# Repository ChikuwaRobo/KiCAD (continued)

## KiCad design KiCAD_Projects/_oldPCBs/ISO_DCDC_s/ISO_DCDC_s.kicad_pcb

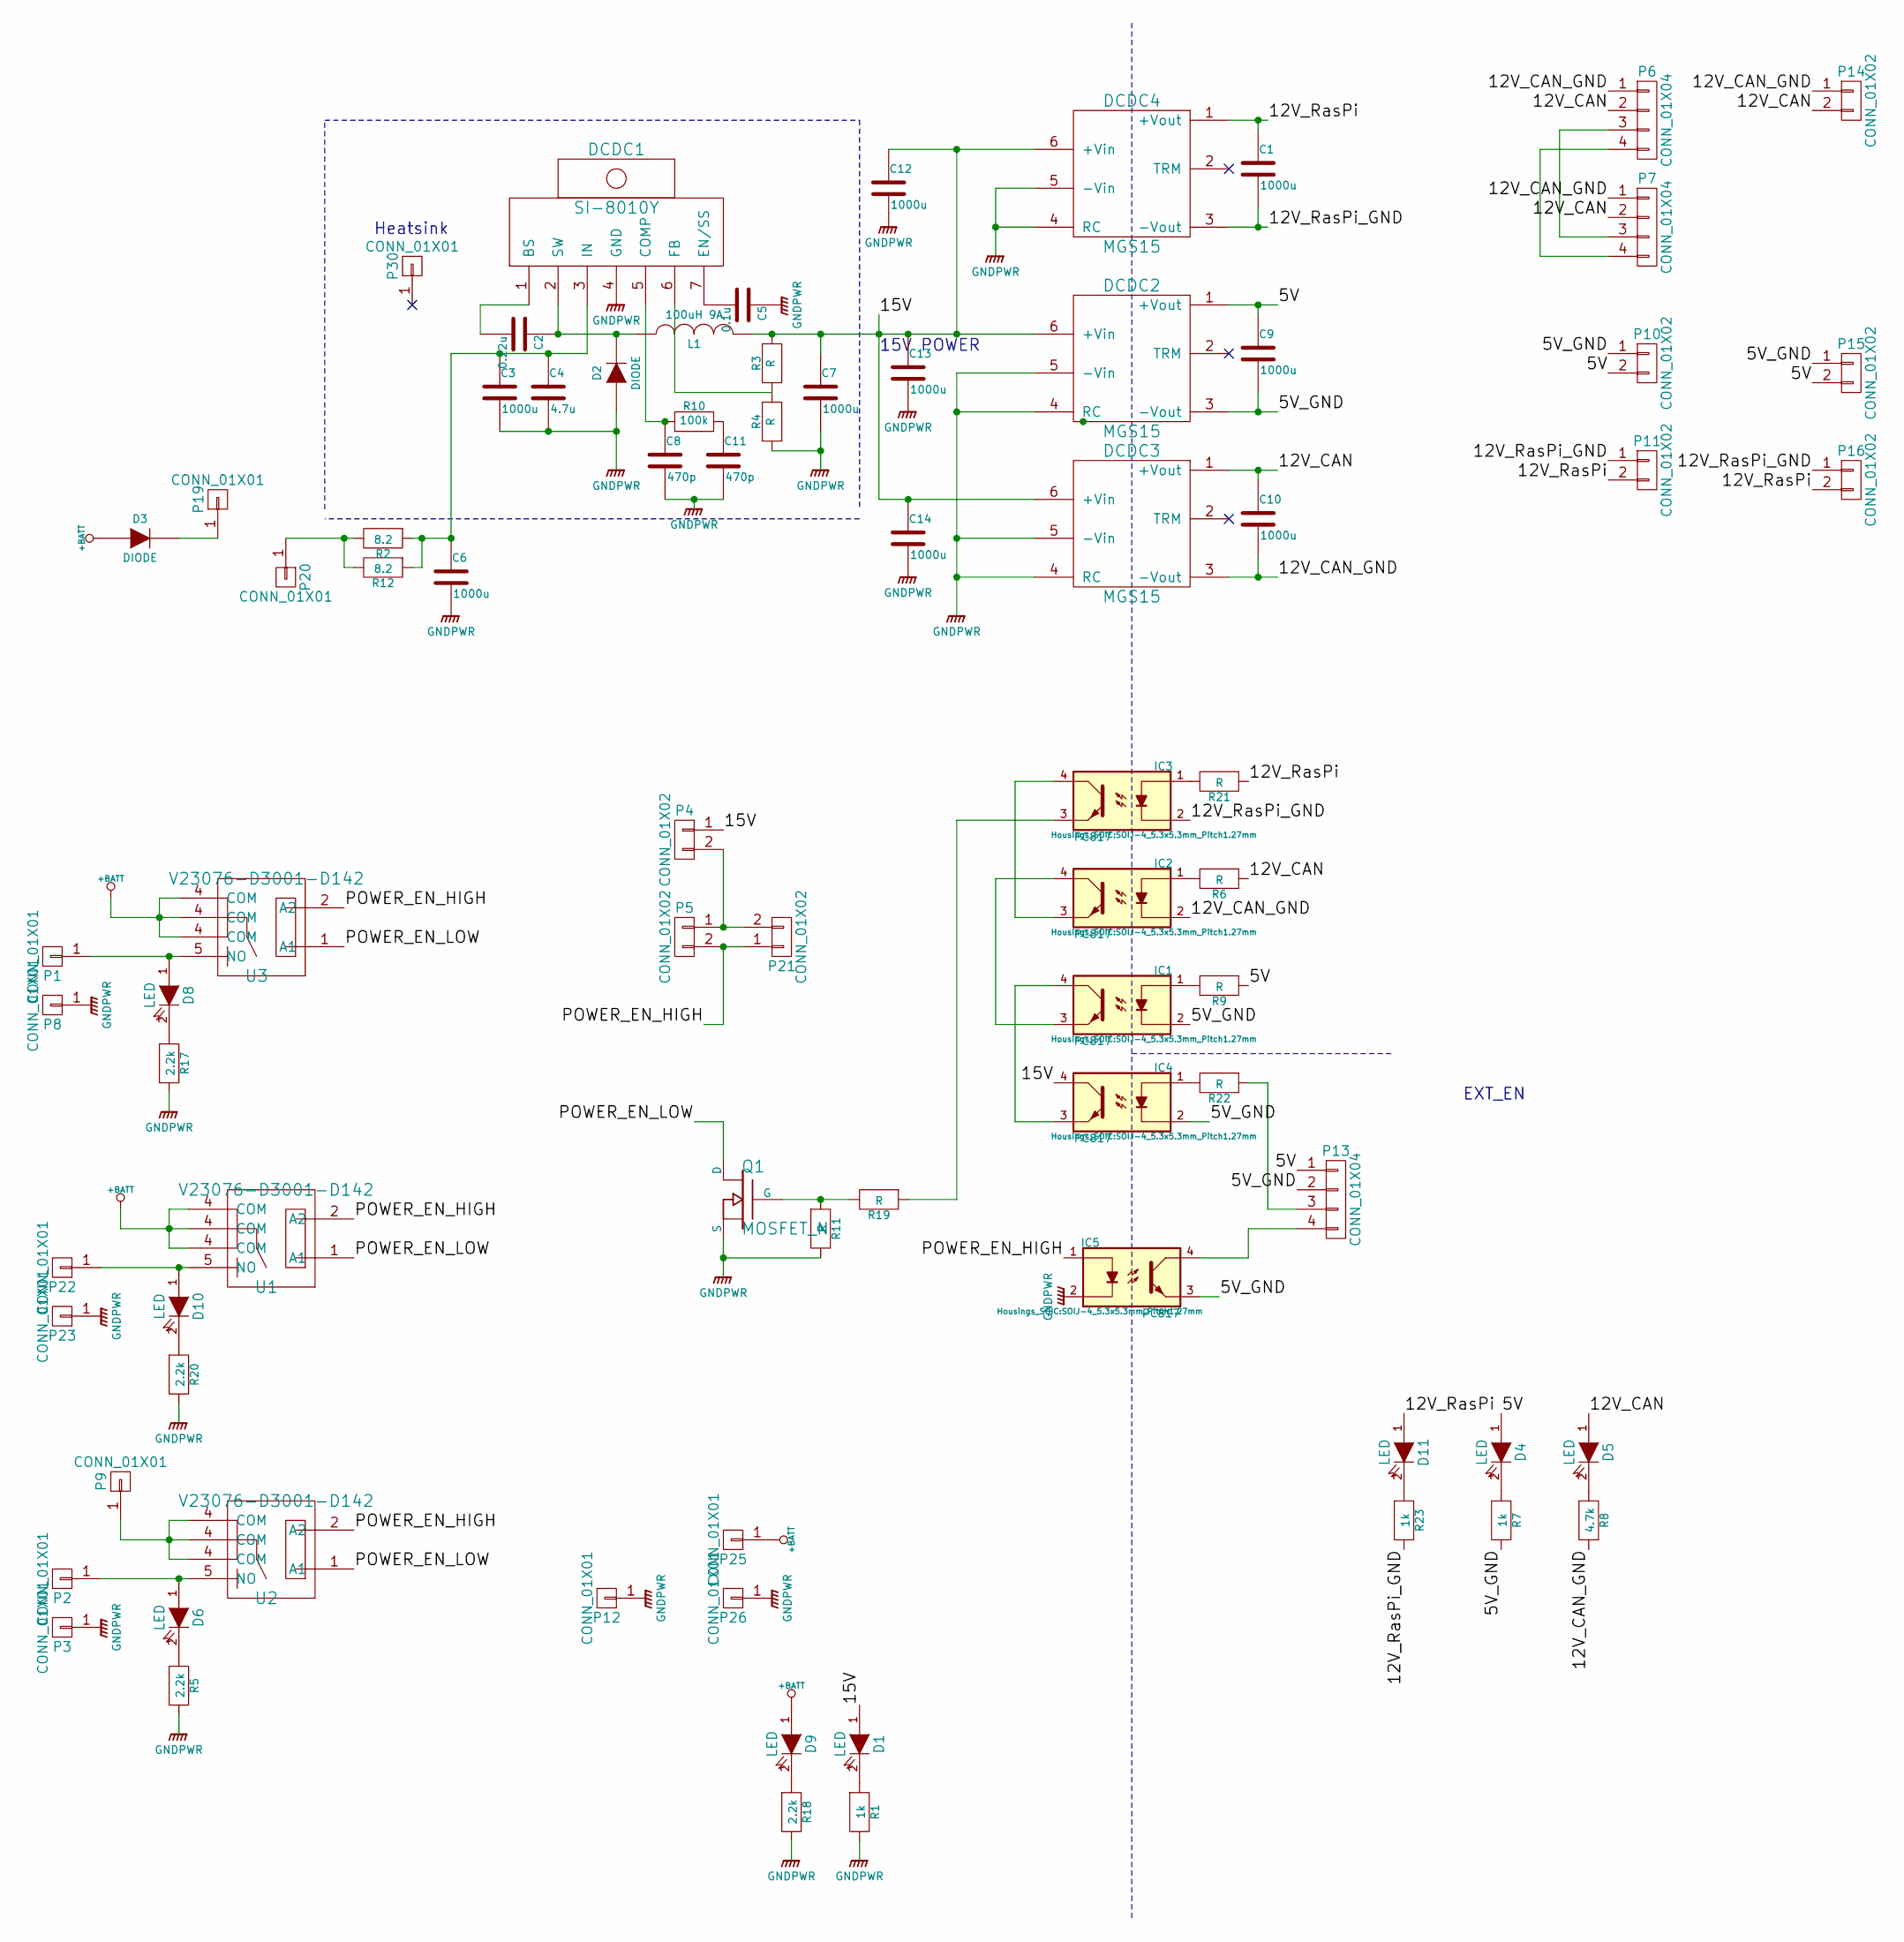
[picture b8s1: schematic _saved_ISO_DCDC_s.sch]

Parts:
C1, C9, C10: 1000u; C_Radial_D8_L11.5_P3.5
C2: 0.22u; C1608_WP
C3, C6, C7, C12, C13, C14: 1000u; C_Radial_D10_L20_P5
C4: 4.7u; C3216
C5: 0.1u; C1608_WP
C8, C11: 470p; C1608_WP
D1, D4, D5, D6, D8, D9, D10, D11: LED; LED-3MM
D2, D3: DIODE; POWER_DI5
DCDC1: SI-8010Y; TO-220_7_Vertical
DCDC2, DCDC3: MGS15
DCDC4: MGS15; MGS30
IC1, IC2, IC3, IC4, IC5: PC817; SOIJ-4_5.3x5.3mm_Pitch1.27mm
L1: 100uH 9A; Choke_Toroid_10x25mm_Vertical
P1, P2, P3, P8, P9, P12, P19, P20, P22, P23, P25, P26: CONN_01X01; 1pin
P4, P5: CONN_01X02; XA_2LC
P6, P7: CONN_01X04; XA_4T
P10, P11, P14, P15, P16: CONN_01X02; XA_2T
P13: CONN_01X04; XA_4LC
P21: CONN_01X02; Pin_Header_Straight_1x02
P30: CONN_01X01; 16PB017_16.25.16
Q1: MOSFET_N; SOT-23_Handsoldering
R1, R7, R23: 1k; C1608_WP
R2, R12: 8.2; R_2512
R3, R4, R6, R9, R11, R21, R22: R; C1608_WP
R5, R17, R18, R20: 2.2k; C1608_WP
R8: 4.7k; C1608_WP
R10: 100k; C1608_WP
R19: R; 0204_2f5
U1, U2, U3: V23076-D3001-D142; V23076-A3001-D142

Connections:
+BATT: D3.2 (A), D9.1 (A), P25.1, U1.4 (COM), U3.4 (COM)
/5V: C9.1, D4.1 (A), DCDC2.1 (+Vout), P10.2, P13.1, P15.2, R9.1
/5V_GND: C9.2, DCDC2.3 (-Vout), IC1.2, IC4.2, IC5.3, P10.1, P13.2, P15.1, R7.2
/12V_CAN: C10.1, D5.1 (A), DCDC3.1 (+Vout), P6.2, P7.2, P14.2, R6.1
/12V_CAN_GND: C10.2, DCDC3.3 (-Vout), IC2.2, P6.1, P7.1, P14.1, R8.2
/12V_RasPi: C1.1, D11.1 (A), DCDC4.1 (+Vout), P11.2, P16.2, R21.1
/12V_RasPi_GND: C1.2, DCDC4.3 (-Vout), IC3.2, P11.1, P16.1, R23.2
/15V: C7.1, C12.1, C13.1, C14.1, D1.1 (A), DCDC2.6 (+Vin), DCDC3.6 (+Vin), DCDC4.6 (+Vin), IC4.4, L1.2, P4.1, R3.2
/POWER_EN_HIGH: IC5.1, P5.2, P21.1, U1.2 (A2), U2.2 (A2), U3.2 (A2)
/POWER_EN_LOW: Q1.D, U1.1 (A1), U2.1 (A1), U3.1 (A1)
GNDPWR: C3.2, C4.2, C5.1, C6.2, C7.2, C8.2, C11.2, C12.2, C13.2, C14.2, D2.2 (A), DCDC1.4 (GND), DCDC2.4 (RC), DCDC2.5 (-Vin), DCDC3.4 (RC), DCDC3.5 (-Vin), DCDC4.4 (RC), DCDC4.5 (-Vin), IC5.2, P3.1, P8.1, P12.1, P23.1, P26.1, Q1.S, R1.2, R4.1, R5.2, R11.2, R17.2, R18.2, R20.2
unnamed: C2.1, D2.1 (K), DCDC1.2 (SW), L1.1
unnamed: C2.2, DCDC1.1 (BS)
unnamed: C3.1, C4.1, C6.1, DCDC1.3 (IN), R2.1, R12.1
unnamed: C5.2, DCDC1.7 (EN/SS)
unnamed: C8.1, DCDC1.5 (COMP), R10.1
unnamed: C11.1, R10.2
unnamed: D1.2 (K), R1.1
unnamed: D3.1 (K), P19.1
unnamed: D4.2 (K), R7.1
unnamed: D5.2 (K), R8.1
unnamed: D6.1 (A), P2.1, U2.5 (NO)
unnamed: D6.2 (K), R5.1
unnamed: D8.1 (A), P1.1, U3.5 (NO)
unnamed: D8.2 (K), R17.1
unnamed: D9.2 (K), R18.1
unnamed: D10.1 (A), P22.1, U1.5 (NO)
unnamed: D10.2 (K), R20.1
unnamed: D11.2 (K), R23.1
unnamed: DCDC1.6 (FB), R3.1, R4.2
unnamed: IC1.1, R9.2
unnamed: IC1.3, IC2.4
unnamed: IC1.4, IC4.3
unnamed: IC2.1, R6.2
unnamed: IC2.3, IC3.4
unnamed: IC3.1, R21.2
unnamed: IC3.3, R19.1
unnamed: IC4.1, R22.2
unnamed: IC5.4, P13.4
unnamed: P6.3, P7.3
unnamed: P6.4, P7.4
unnamed: P9.1, U2.4 (COM)
unnamed: P13.3, R22.1
unnamed: P20.1, R2.2, R12.2
unnamed: P4.2, P5.1, P21.2
unnamed: Q1.G, R11.1, R19.2

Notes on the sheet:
15V POWER
EXT_EN
Heatsink

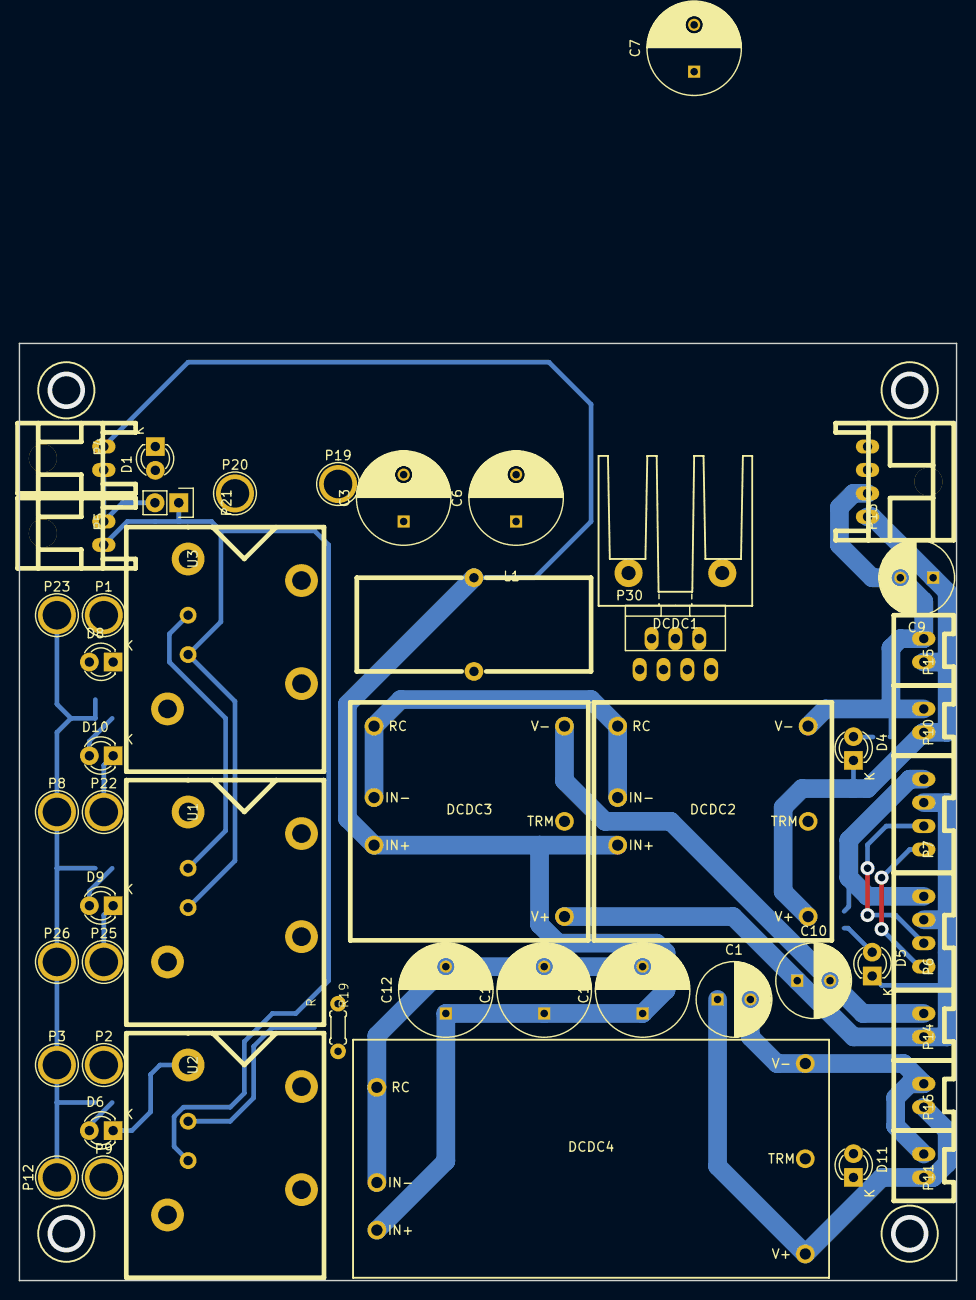
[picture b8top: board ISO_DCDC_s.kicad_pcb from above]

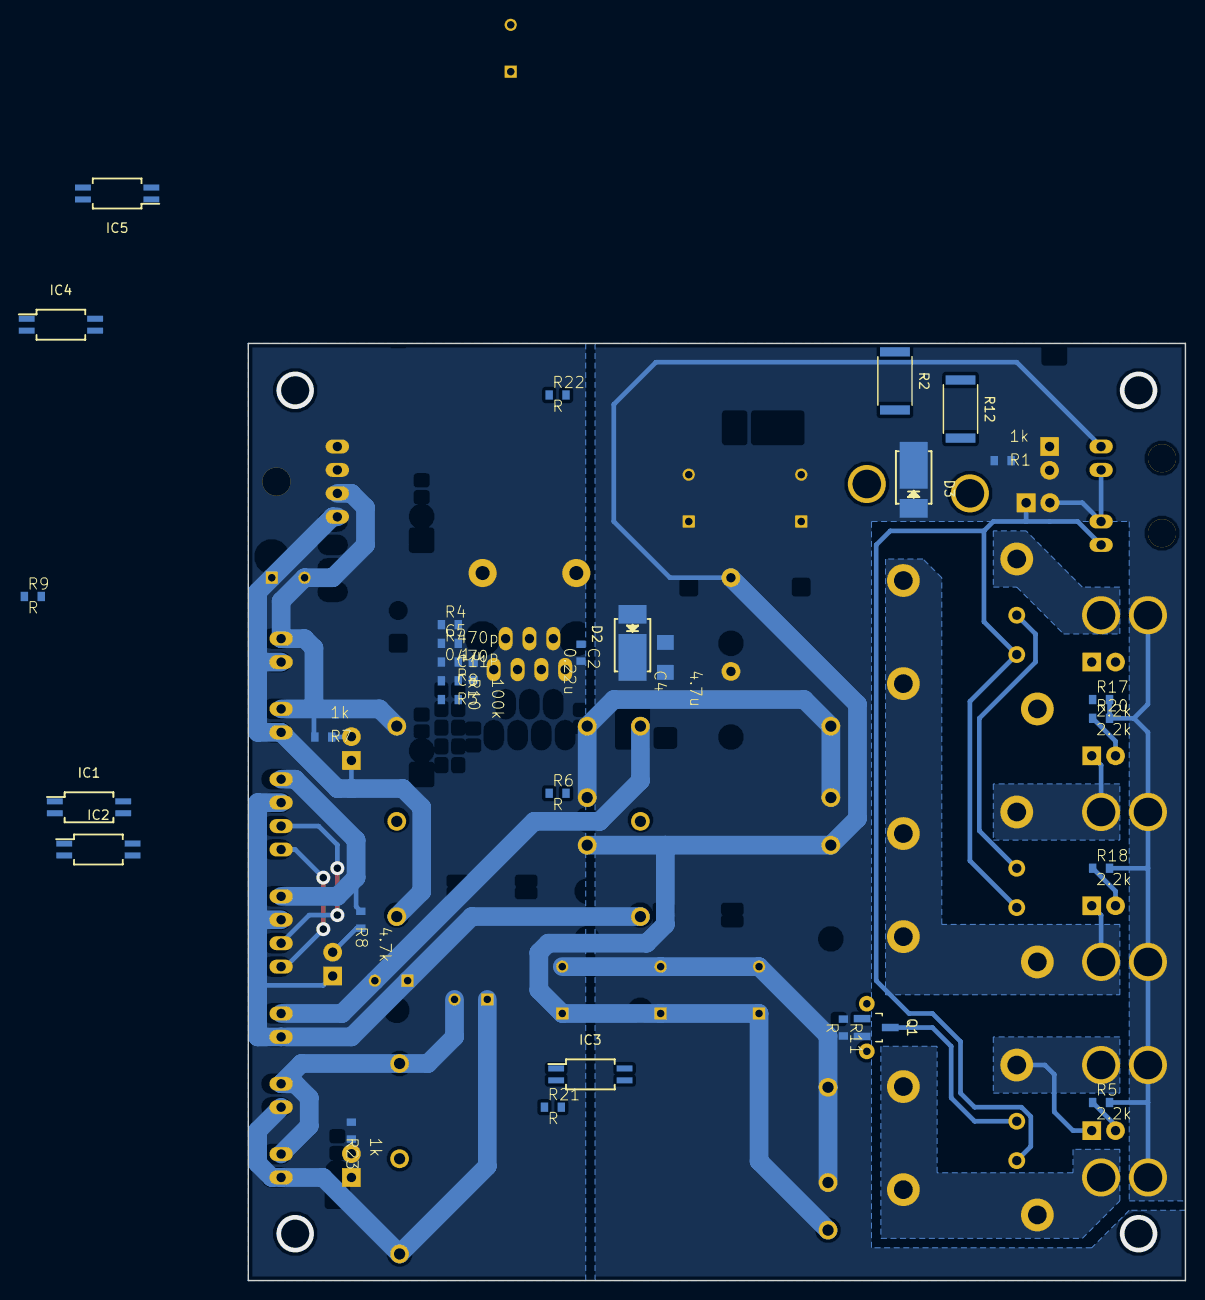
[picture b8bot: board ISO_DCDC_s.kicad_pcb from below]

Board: 2 copper layers, 100.0 x 100.0 mm, 81 parts (31 on the bottom side), 46 nets.
